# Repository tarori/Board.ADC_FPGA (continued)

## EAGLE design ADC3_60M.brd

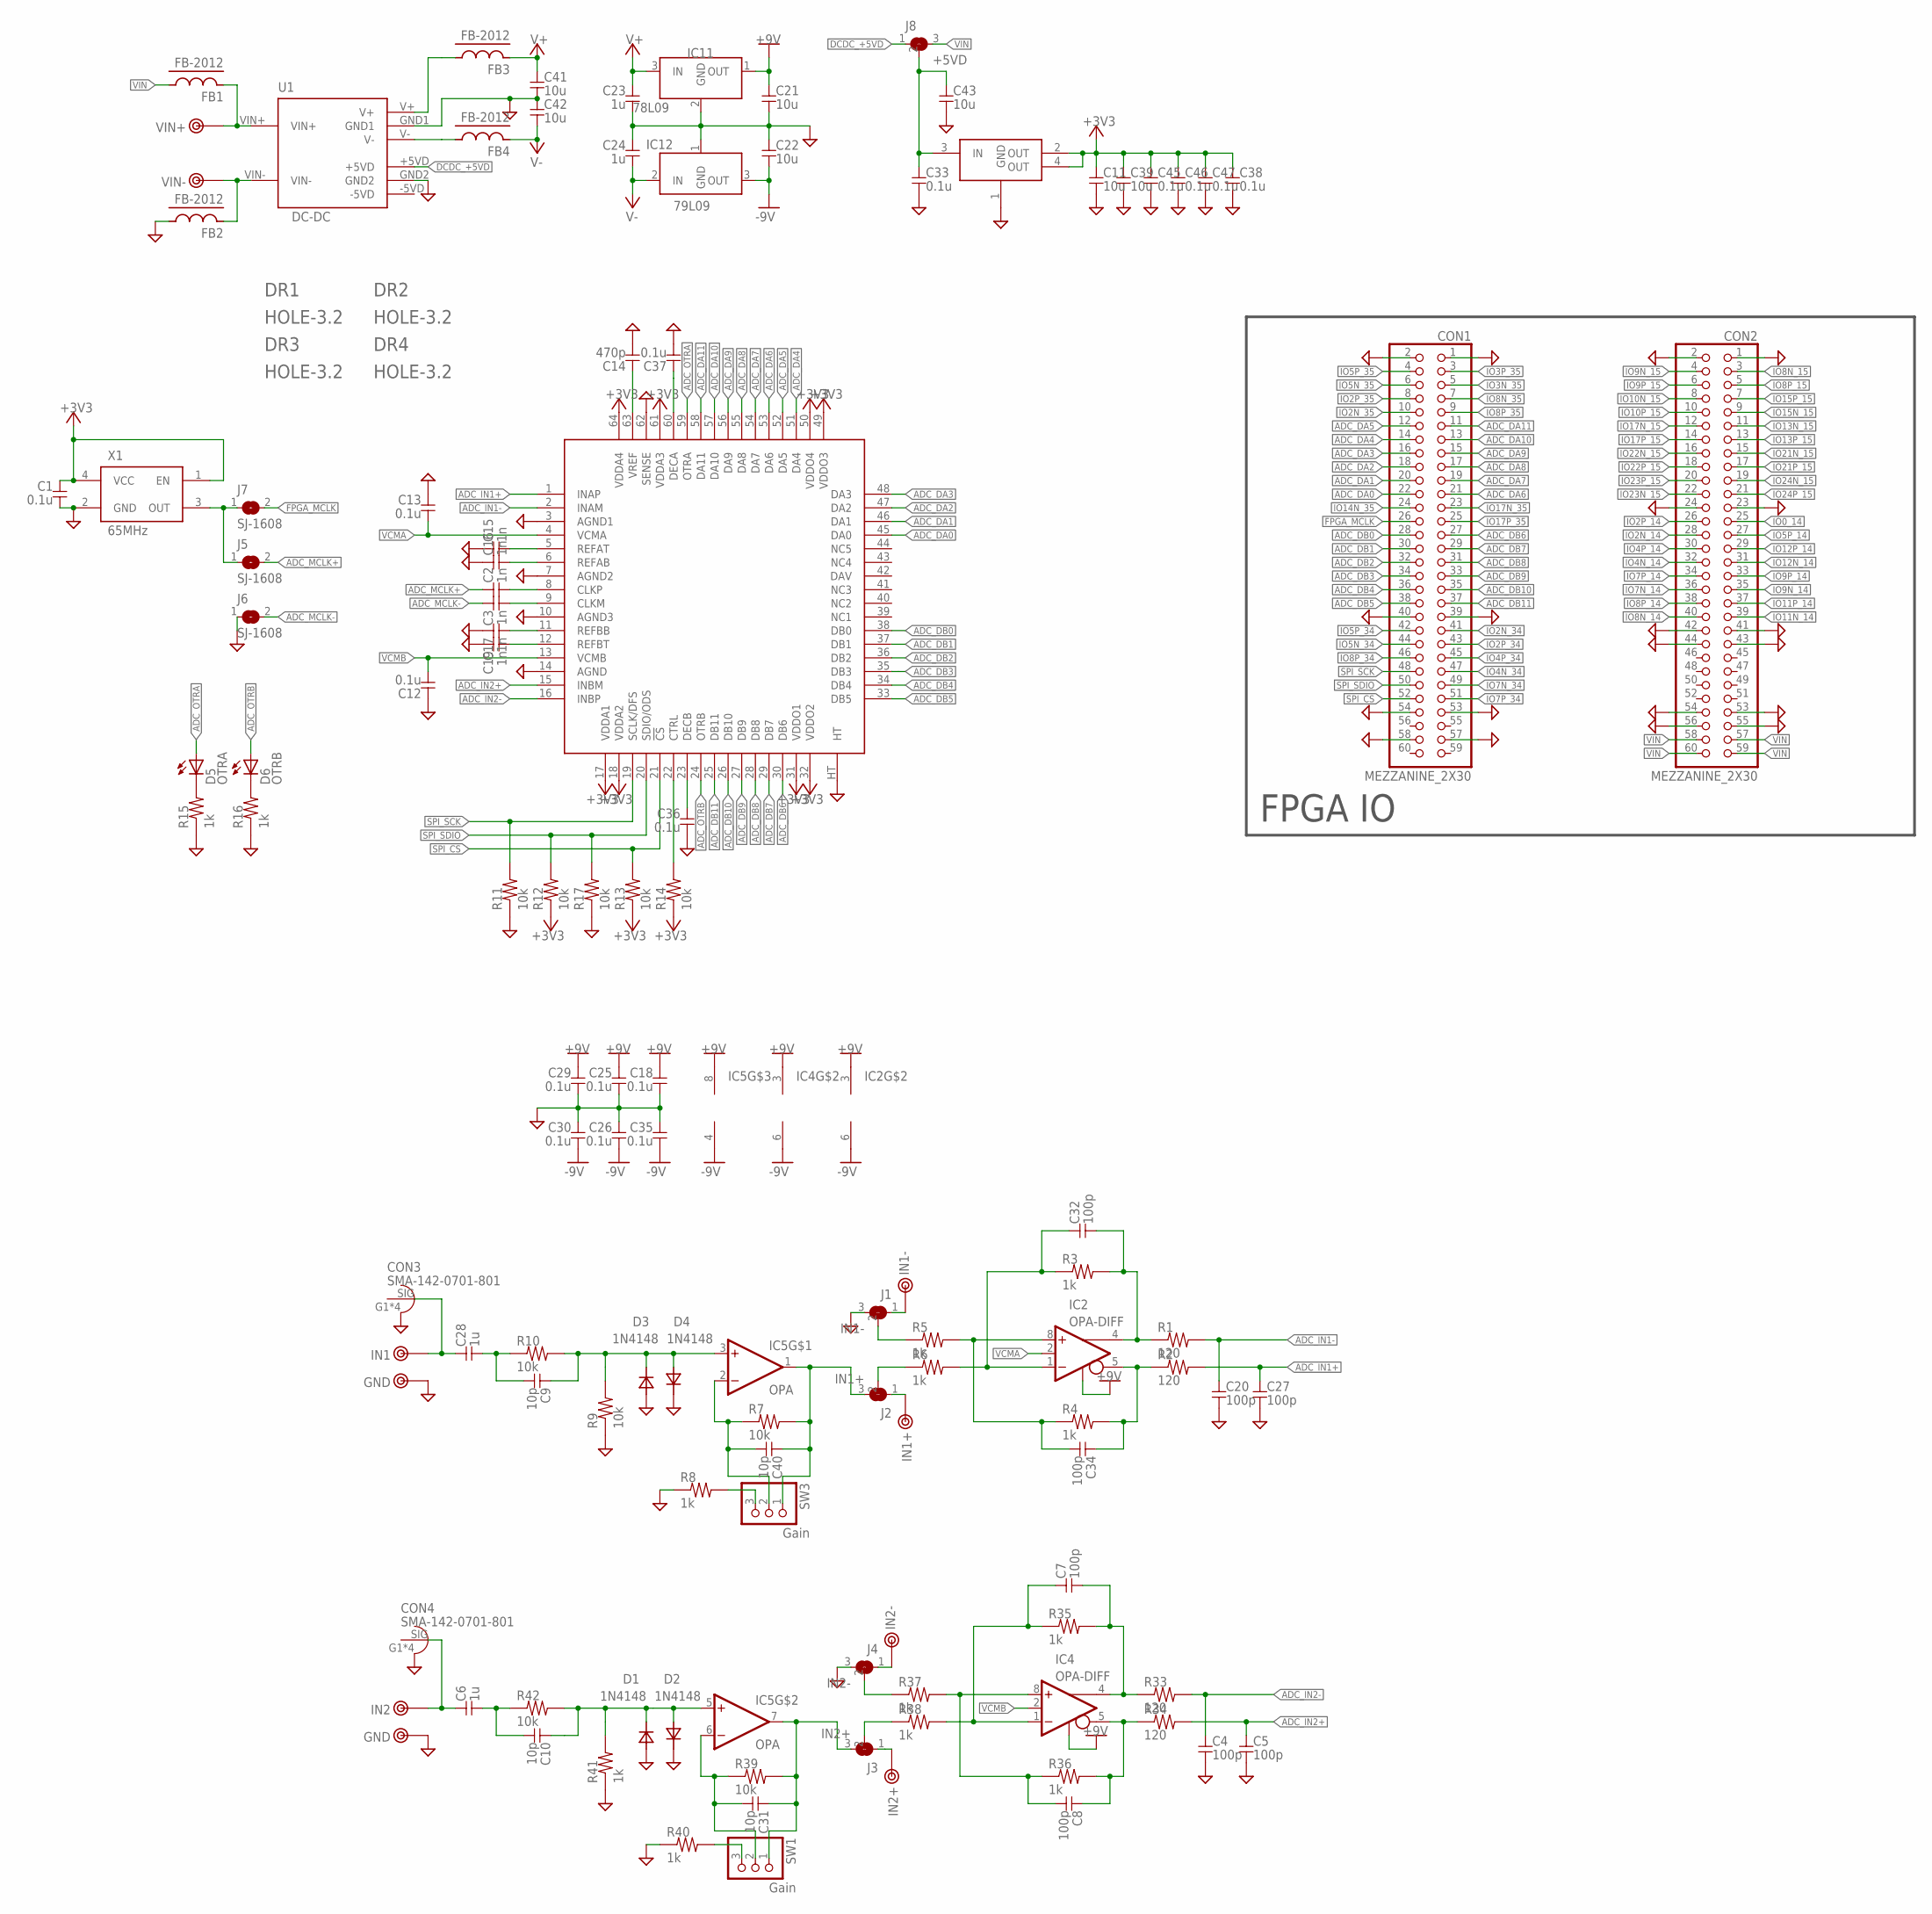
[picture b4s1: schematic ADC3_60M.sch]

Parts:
C1, C12, C13, C18, C25, C26, C29, C30, C33, C35, C36, C37, C38, C45, C46, C47: 0.1u; 1608
C2, C3, C15, C16, C17, C19: 1n; 1608
C4, C5, C7, C8, C20, C27, C32, C34: 100p; 1608
C6, C28: 1u; C050
C9, C10, C31, C40: 10p; 1608
C11, C21, C22, C39, C43: 10u; 2012
C14: 470p; 1608
C23, C24: 1u; 1608
C41, C42: 10u; 3216
CON1, CON2: MEZZANINE_2X30; MEZZANINE_0.8MM_2X30
CON3, CON4: SMA-142-0701-801; SMA-EDGE
D1, D2, D3, D4: 1N4148; SOD123
D5: OTRA; D1608
D6: OTRB; D1608
DR1, DR2, DR3, DR4: HOLE-3.2; HOLE_3.2
FB1, FB2, FB3, FB4: FB-2012; 2012-J
IC1: ADC1212; QFN64HT
IC2, IC4: OPA-DIFF; SOP8
IC5: OPA; SOP8
IC7: AZ1086H-3.3; SOT223
IC11: 78L09; TO-92
IC12: 79L09; TO-92
J1: IN1-; 1608-3-J
J2: IN1+; 1608-3-J
J3: IN2+; 1608-3-J
J4: IN2-; 1608-3-J
J5, J6, J7: SJ-1608; 1608-J
J8: +5VD; 2012-3-J
R1, R2, R33, R34: 120; 1608
R3, R4, R5, R6, R8, R15, R16, R35, R36, R37, R38, R40, R41: 1k; 1608
R7, R9, R10, R11, R12, R13, R14, R17, R39, R42: 10k; 1608
SW1, SW3: Gain; 1X03
TP1: IN2; TESTPIN
TP2, TP5: GND; TESTPIN
TP3: IN2-; TESTPIN
TP4: IN1; TESTPIN
TP6: IN2+; TESTPIN
TP7: IN1-; TESTPIN
TP8: IN1+; TESTPIN
TP30: VIN+; TESTPIN
TP31: VIN-; TESTPIN
U1: DC-DC; DCDC
X1: 65MHz; KC3225

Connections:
+3V3: C1.1, C11.1, C38.1, C39.1, C45.1, C46.1, C47.1, IC1.17 (VDDA1), IC1.18 (VDDA2), IC1.31 (VDDO1), IC1.32 (VDDO2), IC1.49 (VDDO3), IC1.50 (VDDO4), IC1.61 (VDDA3), IC1.64 (VDDA4), IC7.2 (OUT), IC7.4 (OUT), R12.1, R13.1, R14.1, X1.1 (EN), X1.4 (VCC)
+9V: C18.1, C21.1, C25.1, C29.1, IC2.3 (V+), IC2.7 (EN), IC4.3 (V+), IC4.7 (EN), IC5.8 (V+), IC11.1 (OUT)
-9V: C22.2, C26.2, C30.2, C35.2, IC2.6 (V-), IC4.6 (V-), IC5.4 (V-), IC12.3 (OUT)
ADC_DA0: CON1.22, IC1.45 (DA0)
ADC_DA1: CON1.20, IC1.46 (DA1)
ADC_DA2: CON1.18, IC1.47 (DA2)
ADC_DA3: CON1.16, IC1.48 (DA3)
ADC_DA4: CON1.14, IC1.51 (DA4)
ADC_DA5: CON1.12, IC1.52 (DA5)
ADC_DA6: CON1.21, IC1.53 (DA6)
ADC_DA7: CON1.19, IC1.54 (DA7)
ADC_DA8: CON1.17, IC1.55 (DA8)
ADC_DA9: CON1.15, IC1.56 (DA9)
ADC_DA10: CON1.13, IC1.57 (DA10)
ADC_DA11: CON1.11, IC1.58 (DA11)
ADC_DB0: CON1.28, IC1.38 (DB0)
ADC_DB1: CON1.30, IC1.37 (DB1)
ADC_DB2: CON1.32, IC1.36 (DB2)
ADC_DB3: CON1.34, IC1.35 (DB3)
ADC_DB4: CON1.36, IC1.34 (DB4)
ADC_DB5: CON1.38, IC1.33 (DB5)
ADC_DB6: CON1.27, IC1.30 (DB6)
ADC_DB7: CON1.29, IC1.29 (DB7)
ADC_DB8: CON1.31, IC1.28 (DB8)
ADC_DB9: CON1.33, IC1.27 (DB9)
ADC_DB10: CON1.35, IC1.26 (DB10)
ADC_DB11: CON1.37, IC1.25 (DB11)
ADC_IN1+: C27.1, IC1.1 (INAP), R2.2
ADC_IN1-: C20.1, IC1.2 (INAM), R1.2
ADC_IN2+: C5.1, IC1.15 (INBM), R34.2
ADC_IN2-: C4.1, IC1.16 (INBP), R33.2
ADC_MCLK+: C2.1, J5.2
ADC_MCLK-: C3.1, J6.2
ADC_OTRA: D5.A, IC1.59 (OTRA)
ADC_OTRB: D6.A, IC1.24 (OTRB)
DCDC_+5VD: J8.1, U1.+5VD
FPGA_MCLK: CON1.26, J7.2
GND: C1.2, C4.2, C5.2, C11.2, C12.1, C13.1, C14.2, C15.1, C16.1, C17.1, C18.2, C19.1, C20.2, C21.2, C22.1, C23.2, C24.1, C25.2, C26.1, C27.2, C29.2, C30.1, C33.2, C35.1, C36.2, C37.2, C38.2, C39.2, C41.2, C42.1, C43.2, C45.2, C46.2, C47.2, CON1.1, CON1.2, CON1.39, CON1.40, CON1.53, CON1.54, CON1.57, CON1.58, CON2.1, CON2.2, CON2.23, CON2.24, CON2.41, CON2.42, CON2.43, CON2.44, CON2.53, CON2.54, CON2.55, CON2.56, CON3.G1 (GND), CON3.G2 (GND), CON3.G3 (GND), CON3.G4 (GND), CON4.G1 (GND), CON4.G2 (GND), CON4.G3 (GND), CON4.G4 (GND), D1.1 (A), D2.2 (K), D3.1 (A), D4.2 (K), FB2.1, IC1.3 (AGND1), IC1.7 (AGND2), IC1.10 (AGND3), IC1.14 (AGND), IC1.62 (SENSE), IC1.HT, IC7.1 (GND), IC11.2 (GND), IC12.1 (GND), J1.3, J4.3, J6.1, R8.1, R9.1, R11.1, R15.1, R16.1, R17.1, R40.1, R41.1, TP2.1, TP5.1, U1.GND1, U1.GND2, X1.2 (GND)
IO0_14: CON2.25
IO2N_14: CON2.28
IO2N_34: CON1.41
IO2N_35: CON1.10
IO2P_14: CON2.26
IO2P_34: CON1.43
IO2P_35: CON1.8
IO3N_35: CON1.5
IO3P_35: CON1.3
IO4N_14: CON2.32
IO4N_34: CON1.47
IO4P_14: CON2.30
IO4P_34: CON1.45
IO5N_34: CON1.44
IO5N_35: CON1.6
IO5P_14: CON2.27
IO5P_34: CON1.42
IO5P_35: CON1.4
IO7N_14: CON2.36
IO7N_34: CON1.49
IO7P_14: CON2.34
IO7P_34: CON1.51
IO8N_14: CON2.40
IO8N_15: CON2.3
IO8N_35: CON1.7
IO8P_14: CON2.38
IO8P_15: CON2.5
IO8P_34: CON1.46
IO8P_35: CON1.9
IO9N_14: CON2.35
IO9N_15: CON2.4
IO9P_14: CON2.33
IO9P_15: CON2.6
IO10N_15: CON2.8
IO10P_15: CON2.10
IO11N_14: CON2.39
IO11P_14: CON2.37
IO12N_14: CON2.31
IO12P_14: CON2.29
IO13N_15: CON2.11
IO13P_15: CON2.13
IO14N_35: CON1.24
IO15N_15: CON2.9
IO15P_15: CON2.7
IO17N_15: CON2.12
IO17N_35: CON1.23
IO17P_15: CON2.14
IO17P_35: CON1.25
IO21N_15: CON2.15
IO21P_15: CON2.17
IO22N_15: CON2.16
IO22P_15: CON2.18
IO23N_15: CON2.22
IO23P_15: CON2.20
IO24N_15: CON2.19
IO24P_15: CON2.21
MCLK: J5.1, J7.1, X1.3 (OUT)
unnamed: C7.2, IC4.4 (+OUT), R33.1, R35.2
unnamed: C8.1, IC4.5 (-OUT), R34.1, R36.2
unnamed: C8.2, IC4.8 (+IN), R36.1, R37.2
unnamed: R40.2, SW1.3
unnamed: C3.2, IC1.9 (CLKM)
unnamed: C2.2, IC1.8 (CLKP)
unnamed: C14.1, IC1.63 (VREF)
unnamed: C17.2, IC1.11 (REFBB)
unnamed: C19.2, IC1.12 (REFBT)
unnamed: C15.2, IC1.5 (REFAT)
unnamed: C16.2, IC1.6 (REFAB)
unnamed: C7.1, IC4.1 (-IN), R35.1, R38.2
unnamed: C32.2, IC2.4 (+OUT), R1.1, R3.2
unnamed: C34.1, IC2.5 (-OUT), R2.1, R4.2
unnamed: J3.1, TP6.1
unnamed: C31.2, IC5.6 (-IN), R39.1, SW1.2
unnamed: C34.2, IC2.8 (+IN), R4.1, R5.2
unnamed: C32.1, IC2.1 (-IN), R3.1, R6.2
unnamed: C40.1, IC5.1 (OUT), J2.3, R7.2, SW3.1
unnamed: C40.2, IC5.2 (-IN), R7.1, SW3.2
unnamed: C6.1, CON4.SIG, TP1.1
unnamed: C9.2, C28.2, R10.1
unnamed: C9.1, D3.2 (K), D4.1 (A), IC5.3 (+IN), R9.2, R10.2
unnamed: R8.2, SW3.3
unnamed: J1.2, R5.1
unnamed: J2.2, R6.1
unnamed: J3.2, R38.1
unnamed: C28.1, CON3.SIG, TP4.1
unnamed: J4.2, R37.1
unnamed: C31.1, IC5.7 (OUT), J3.3, R39.2, SW1.1
unnamed: J4.1, TP3.1
unnamed: J2.1, TP8.1
unnamed: J1.1, TP7.1
unnamed: C33.1, C43.1, IC7.3 (IN), J8.2
unnamed: C6.2, C10.2, R42.1
unnamed: C10.1, D1.2 (K), D2.1 (A), IC5.5 (+IN), R41.2, R42.2
unnamed: C37.1, IC1.60 (DECA)
unnamed: D6.K, R16.2
unnamed: D5.K, R15.2
unnamed: IC1.22 (CTRL), R14.2
unnamed: C36.1, IC1.23 (DECB)
unnamed: FB1.2, TP30.1, U1.VIN+
unnamed: FB2.2, TP31.1, U1.VIN-
SPI_CS: CON1.52, IC1.21 (!CS), R13.2
SPI_SCK: CON1.48, IC1.19 (SCLK/DFS), R11.2
SPI_SDIO: CON1.50, IC1.20 (SDIO/ODS), R12.2, R17.2
V+: C23.1, C41.1, FB3.2, IC11.3 (IN)
V+_DCDC: FB3.1, U1.V+
V-: C24.2, C42.2, FB4.2, IC12.2 (IN)
V-_DCDC: FB4.1, U1.V-
VCMA: C13.2, IC1.4 (VCMA), IC2.2 (CM)
VCMB: C12.2, IC1.13 (VCMB), IC4.2 (CM)
VIN: CON2.57, CON2.58, CON2.59, CON2.60, FB1.1, J8.3

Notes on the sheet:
FPGA IO

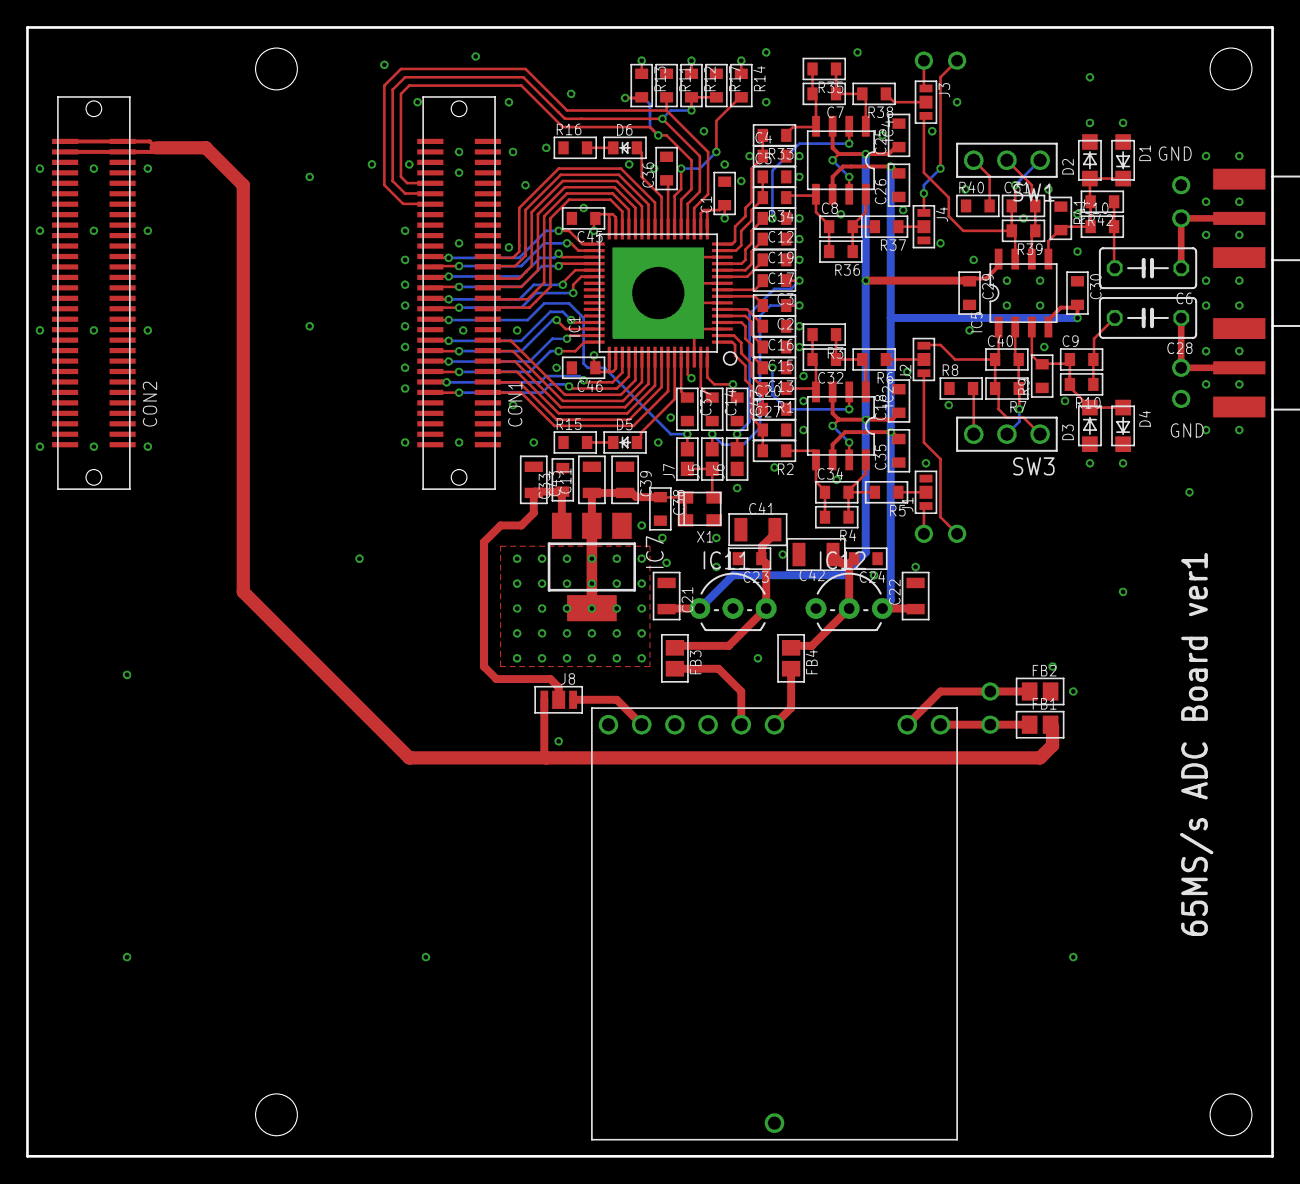
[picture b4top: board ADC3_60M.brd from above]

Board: 4 copper layers, 95.2 x 86.4 mm, 120 parts (0 on the bottom side), 92 nets.

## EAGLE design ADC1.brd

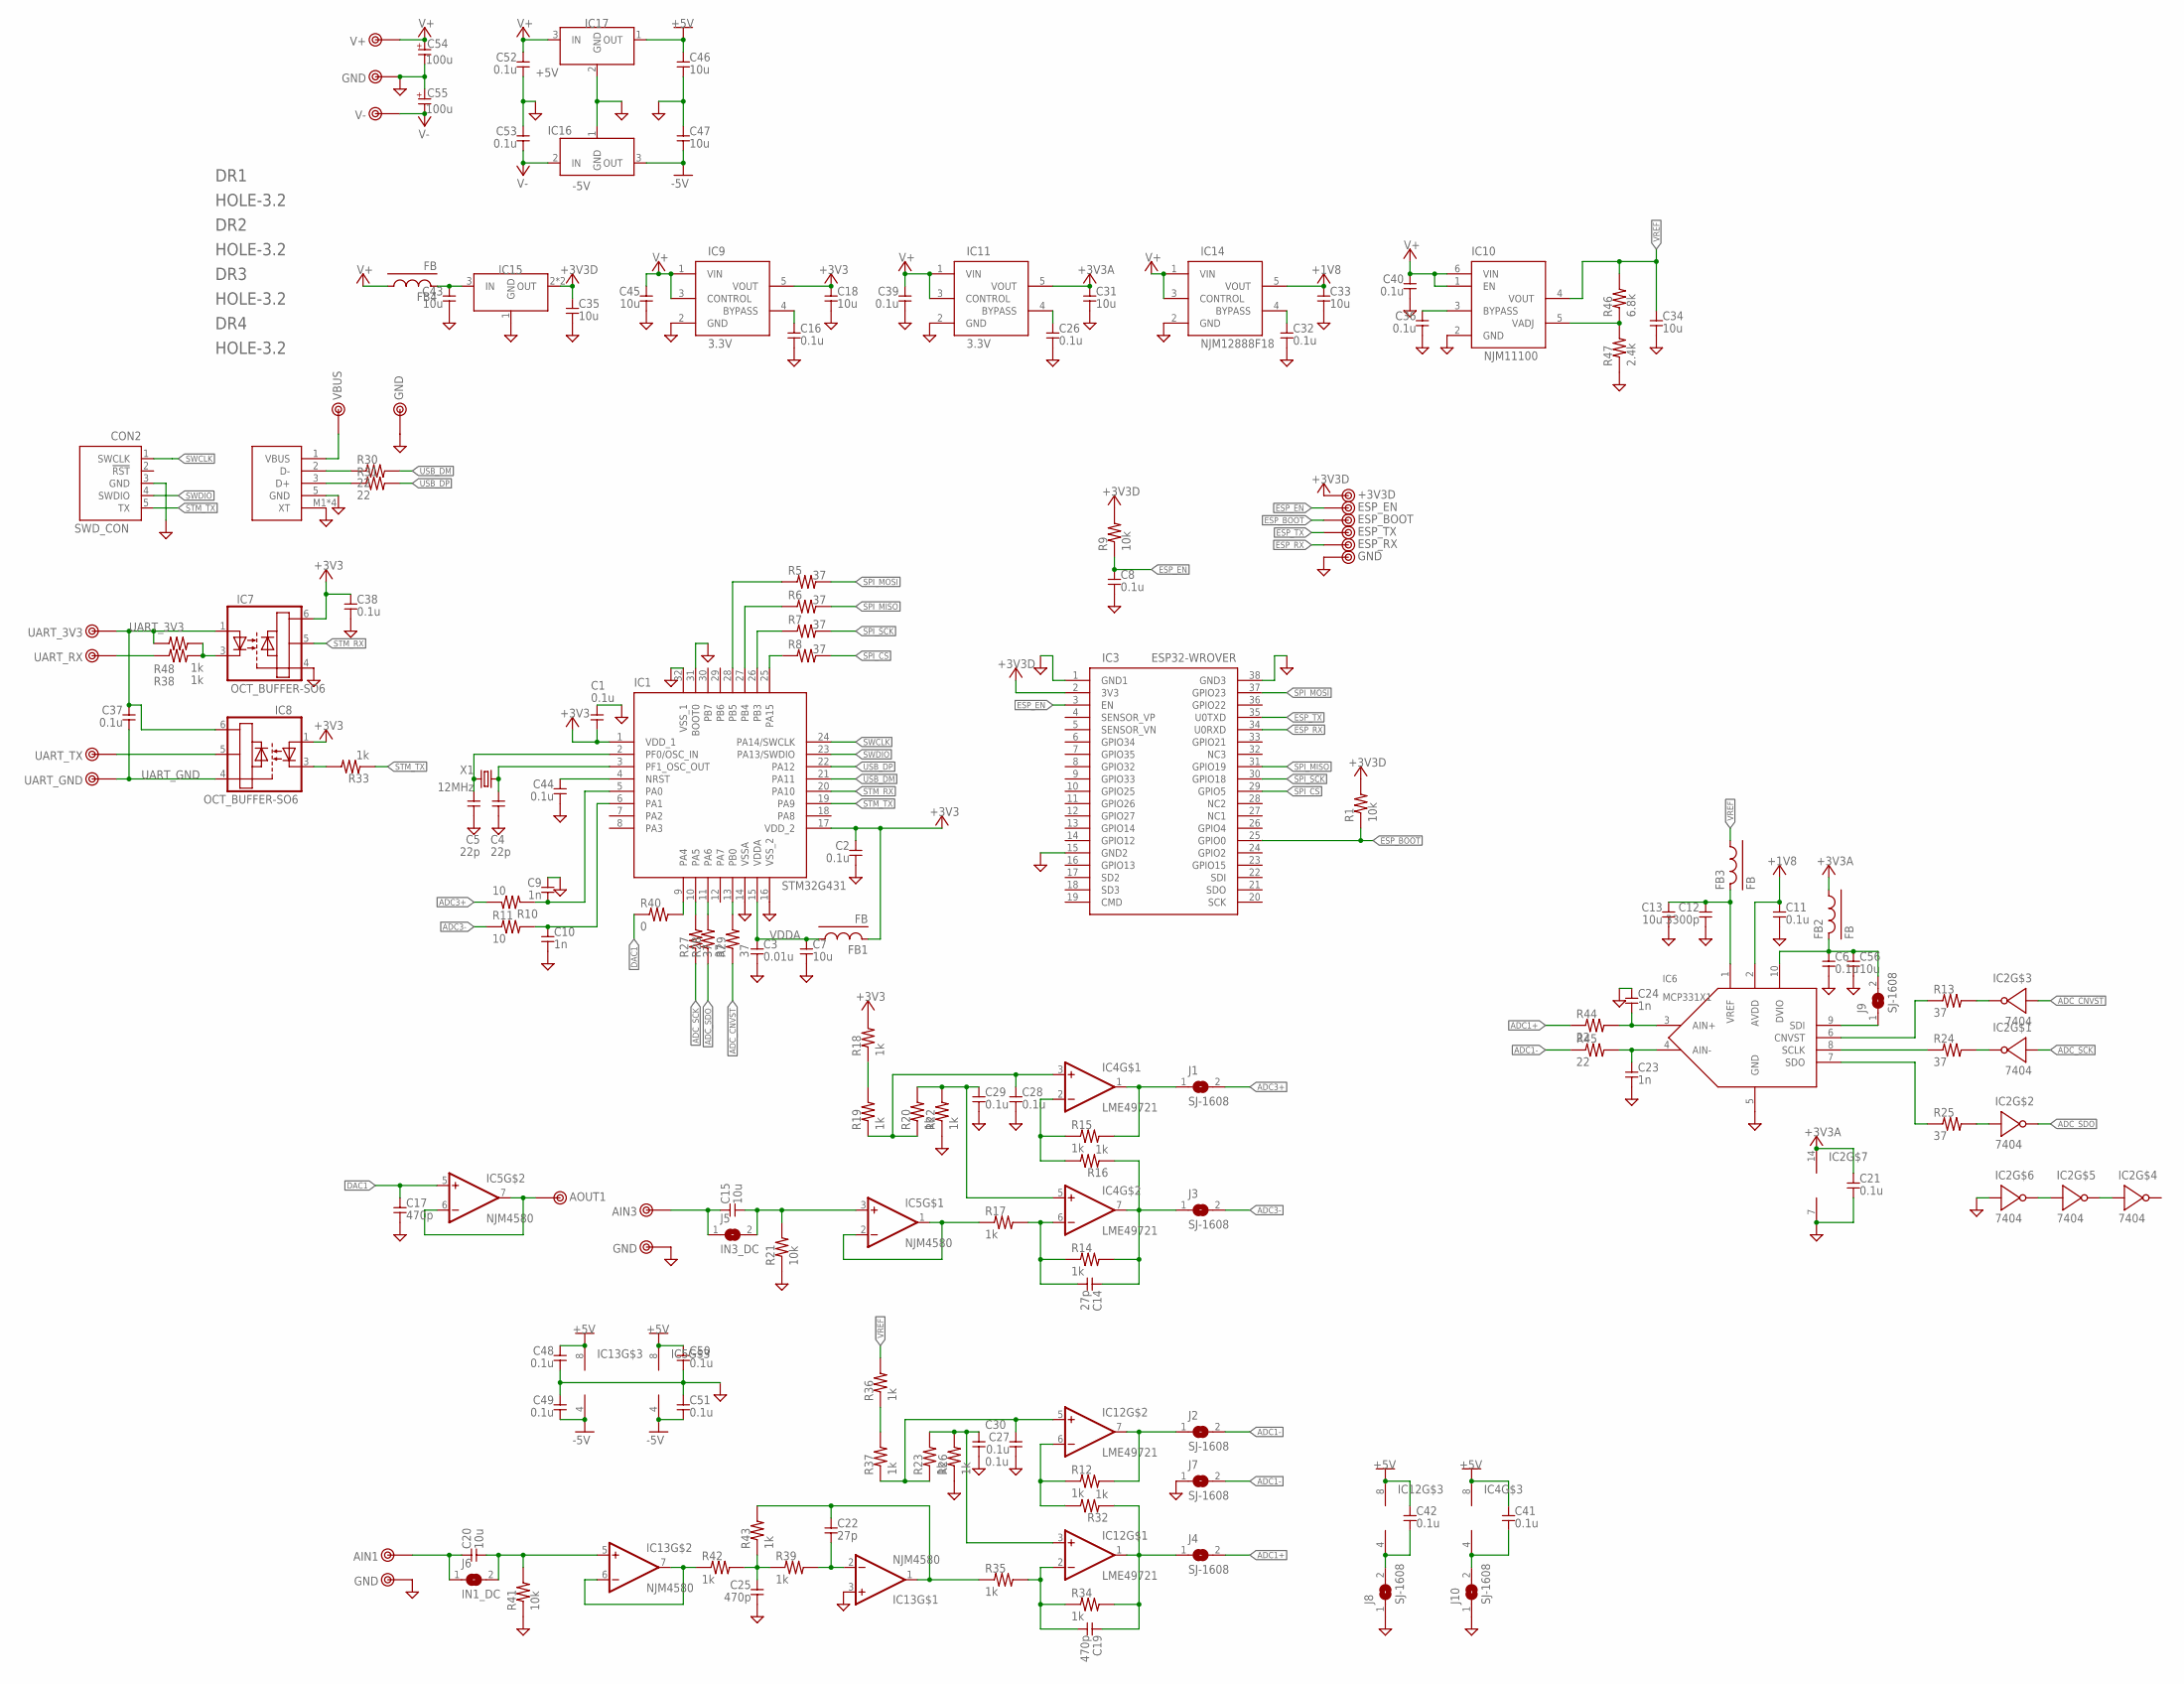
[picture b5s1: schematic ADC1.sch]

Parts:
C1, C2, C6, C8, C11, C16, C21, C26, C27, C28, C29, C30, C32, C36, C37, C38, C39, C40, C41, C42, C44, C48, C49, C50, C51, C52, C53: 0.1u; 1608
C3: 0.01u; 1608
C4, C5: 22p; 1608
C7, C13, C18, C31, C33, C34, C35, C43, C45, C46, C47, C56: 10u; 2012
C9, C10, C23, C24: 1n; 1608
C12: 3300p; 1608
C14, C22: 27p; 1608
C15, C20: 10u; 3225
C17, C19, C25: 470p; 1608
C54, C55: 100u; E2,5-8
CON1: USB-A; UX60A-MB-5ST
CON2: SWD_CON
DR1, DR2, DR3, DR4: HOLE-3.2; HOLE_3.2
FB1, FB2, FB3, FB4: FB; 1608-J
IC1: STM32G431; TQFP32-08
IC2: 7404; TSSOP14
IC3: ESP32-WROVER
IC4, IC12: LME49721; SOP8
IC5, IC13: NJM4580; SOP8
IC6: MCP331X1; MSOP10
IC7, IC8: OCT_BUFFER-SO6; SO6
IC9, IC11: 3.3V; SOT23-5
IC10: NJM11100; SOT23-6
IC14: NJM12888F18; SOT23-5
IC15: LM1117GS; SOT223
IC16: -5V; TO-92
IC17: +5V; TO-92
J1, J2, J3, J4, J7, J8, J9, J10: SJ-1608; 1608-J
J5: IN3_DC; 2012-J
J6: IN1_DC; 2012-J
R1, R9, R21, R41: 10k; 1608
R5, R6, R7, R8, R13, R24, R25, R27, R28, R29: 37; 1608-J
R10, R11: 10; 1608
R12, R14, R15, R16, R17, R18, R19, R20, R22, R23, R26, R32, R33, R34, R35, R36, R37, R38, R39, R42, R43, R48: 1k; 1608
R30, R31, R44, R45: 22; 1608
R40: 0; 1608-J
R46: 6.8k; 1608
R47: 2.4k; 1608
TP1: AIN3; TESTPIN-BIG
TP2: AIN1; TESTPIN-BIG
TP3: AOUT1; TESTPIN-BIG
TP4: VBUS; TESTPIN
TP5: UART_3V3; TESTPIN
TP6: UART_RX; TESTPIN
TP7: UART_GND; TESTPIN
TP8: UART_TX; TESTPIN
TP9: +3V3D; TESTPIN
TP10: ESP_EN; TESTPIN
TP11: ESP_BOOT; TESTPIN
TP12: ESP_TX; TESTPIN
TP13, TP20: GND; TESTPIN
TP14: ESP_RX; TESTPIN
TP15, TP16, TP18: GND; TESTPIN-BIG
TP17: V+; TESTPIN-BIG
TP19: V-; TESTPIN-BIG
X1: 12MHz; HC49/S

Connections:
+1V8: C11.1, C33.1, IC6.2 (AVDD), IC14.5 (VOUT)
+3V3: C1.2, C2.1, C18.1, C38.1, FB1.2, IC1.1 (VDD_1), IC1.17 (VDD_2), IC7.6 (V+), IC8.1 (A), IC9.5 (VOUT), R18.2
+3V3A: C21.1, C31.1, FB2.1, IC2.14 (V+), IC11.5 (VOUT)
+3V3D: C35.1, IC3.2 (3V3), IC15.2 (OUT), IC15.4 (OUT), R1.2, R9.2, TP9.1
+5V: C41.1, C42.1, C46.1, C48.1, C50.1, IC4.8 (V+), IC5.8 (V+), IC12.8 (V+), IC13.8 (V+), IC17.1 (OUT)
-5V: C47.2, C49.2, C51.2, IC5.4 (V-), IC13.4 (V-), IC16.3 (OUT)
ADC1+: J4.2, R44.1
ADC1-: J2.2, J7.2, R45.1
ADC3+: J1.2, R10.1
ADC3-: J3.2, R11.1
ADC_CNVST: IC2.5 (IN), R29.1
ADC_SCK: IC2.1 (IN), R27.1
ADC_SDO: IC2.4 (OUT), R28.1
DAC1: C17.1, IC5.5 (+IN), R40.1
ESP_BOOT: IC3.25 (GPIO0), R1.1, TP11.1
ESP_EN: C8.1, IC3.3 (EN), R9.1, TP10.1
ESP_RX: IC3.34 (U0RXD), TP14.1
ESP_TX: IC3.35 (U0TXD), TP12.1
GND: C1.1, C2.2, C3.2, C4.2, C5.2, C6.2, C7.2, C8.2, C9.1, C10.2, C11.2, C12.2, C13.2, C16.2, C17.2, C18.2, C21.2, C23.2, C24.1, C25.2, C26.2, C27.2, C28.2, C29.2, C30.2, C31.2, C32.2, C33.2, C34.2, C35.2, C36.2, C38.2, C39.2, C40.2, C43.2, C44.2, C45.2, C46.2, C47.1, C48.2, C49.1, C50.2, C51.1, C52.2, C53.1, C54.- (2), C55.+ (1), C56.2, CON1.5 (GND), CON1.M1 (XT), CON1.M2 (XT), CON1.M3 (XT), CON1.M4 (XT), CON2.3 (GND), IC1.14 (VSSA), IC1.16 (VSS_2), IC1.31 (BOOT0), IC1.32 (VSS_1), IC2.7 (V-), IC2.13 (IN), IC3.1 (GND1), IC3.15 (GND2), IC3.38 (GND3), IC6.5 (GND), IC7.4 (GND), IC9.2 (GND), IC10.2 (GND), IC11.2 (GND), IC13.3 (+IN), IC14.2 (GND), IC15.1 (GND), IC16.1 (GND), IC17.2 (GND), J7.1, J8.1, J10.1, R21.1, R22.1, R26.1, R41.1, R47.1, TP13.1, TP15.1, TP16.1, TP18.1, TP20.1
unnamed: C5.1, IC1.2 (PF0/OSC_IN), X1.2
unnamed: C9.2, IC1.5 (PA0), R10.2
unnamed: C4.1, IC1.3 (PF1_OSC_OUT), X1.1
unnamed: C25.1, R39.1, R42.2, R43.1
unnamed: C10.1, IC1.6 (PA1), R11.2
unnamed: IC1.26 (PB3), R7.1
unnamed: IC1.27 (PB4), R6.1
unnamed: IC1.28 (PB5), R5.1
unnamed: IC1.13 (PB0), R29.2
unnamed: C15.1, J5.1, TP1.1
unnamed: IC2.11 (IN), IC2.12 (OUT)
unnamed: IC2.9 (IN), IC2.10 (OUT)
unnamed: C28.1, IC4.3 (+IN), R19.1, R20.1
unnamed: C6.1, C56.1, FB2.2, IC6.10 (DVIO), J9.2
unnamed: C12.1, C13.1, FB3.2, IC6.1 (VREF)
unnamed: IC1.25 (PA15), R8.1
unnamed: IC4.2 (-IN), R15.1, R16.2
unnamed: IC2.6 (OUT), R13.2
unnamed: IC2.3 (IN), R25.2
unnamed: C14.2, IC4.6 (-IN), R14.1, R17.2
unnamed: C15.2, IC5.3 (+IN), J5.2, R21.2
unnamed: IC5.1 (OUT), IC5.2 (-IN), R17.1
unnamed: IC5.6 (-IN), IC5.7 (OUT), TP3.1
unnamed: IC6.7 (SDO), R25.1
unnamed: IC4.1 (OUT), J1.1, R15.2
unnamed: C14.1, IC4.7 (OUT), J3.1, R14.2, R16.1
unnamed: IC6.8 (SCLK), R24.1
unnamed: IC6.6 (CNVST), R13.1
unnamed: IC6.9 (SDI), J9.1
unnamed: IC2.2 (OUT), R24.2
unnamed: CON1.2 (D-), R30.1
unnamed: CON1.3 (D+), R31.1
unnamed: IC8.3 (C), R33.2
unnamed: IC7.3 (C), R38.2, R48.2
unnamed: IC1.10 (PA5), R27.2
unnamed: IC1.11 (PA6), R28.2
unnamed: R36.1, R37.2
unnamed: C29.1, IC4.5 (+IN), R20.2, R22.2
unnamed: R18.1, R19.2
unnamed: C27.1, IC12.5 (+IN), R23.1, R37.1
unnamed: IC12.6 (-IN), R12.1, R32.2
unnamed: C19.2, IC12.2 (-IN), R34.1, R35.2
unnamed: C30.1, IC12.3 (+IN), R23.2, R26.2
unnamed: IC13.6 (-IN), IC13.7 (OUT), R42.1
unnamed: IC12.7 (OUT), J2.1, R12.2
unnamed: C19.1, IC12.1 (OUT), J4.1, R32.1, R34.2
unnamed: C20.1, J6.1, TP2.1
unnamed: C20.2, IC13.5 (+IN), J6.2, R41.2
unnamed: C16.1, IC9.4 (BYPASS)
unnamed: C24.2, IC6.3 (AIN+), R44.2
unnamed: C23.1, IC6.4 (AIN-), R45.2
unnamed: IC1.9 (PA4), R40.2
unnamed: C22.2, IC13.2 (-IN), R39.2
unnamed: C26.1, IC11.4 (BYPASS)
unnamed: C22.1, IC13.1 (OUT), R35.1, R43.2
unnamed: C32.1, IC14.4 (BYPASS)
unnamed: C36.1, IC10.3 (BYPASS)
unnamed: IC10.5 (VADJ), R46.1, R47.2
unnamed: C42.2, IC12.4 (V-), J8.2
unnamed: C41.2, IC4.4 (V-), J10.2
unnamed: C43.1, FB4.2, IC15.3 (IN)
unnamed: C44.1, IC1.4 (NRST)
SPI_CS: IC3.29 (GPIO5), R8.2
SPI_MISO: IC3.31 (GPIO19), R6.2
SPI_MOSI: IC3.37 (GPIO23), R5.2
SPI_SCK: IC3.30 (GPIO18), R7.2
STM_RX: IC1.20 (PA10), IC7.5 (OUT)
STM_TX: CON2.5 (TX), IC1.19 (PA9), R33.1
SWCLK: CON2.1 (SWCLK), IC1.24 (PA14/SWCLK)
SWDIO: CON2.4 (SWDIO), IC1.23 (PA13/SWDIO)
UART_3V3: C37.1, IC7.1 (A), IC8.6 (V+), R48.1, TP5.1
UART_GND: C37.2, IC8.4 (GND), TP7.1
UART_RX: R38.1, TP6.1
UART_TX: IC8.5 (OUT), TP8.1
USB_DM: IC1.21 (PA11), R30.2
USB_DP: IC1.22 (PA12), R31.2
V+: C39.1, C40.1, C45.1, C52.1, C54.+ (1), FB4.1, IC9.1 (VIN), IC9.3 (CONTROL), IC10.1 (EN), IC10.6 (VIN), IC11.1 (VIN), IC11.3 (CONTROL), IC14.1 (VIN), IC14.3 (CONTROL), IC17.3 (IN), TP17.1
V-: C53.2, C55.- (2), IC16.2 (IN), TP19.1
VBUS: CON1.1 (VBUS), TP4.1
VDDA: C3.1, C7.1, FB1.1, IC1.15 (VDDA)
VREF: C34.1, FB3.1, IC10.4 (VOUT), R36.2, R46.2

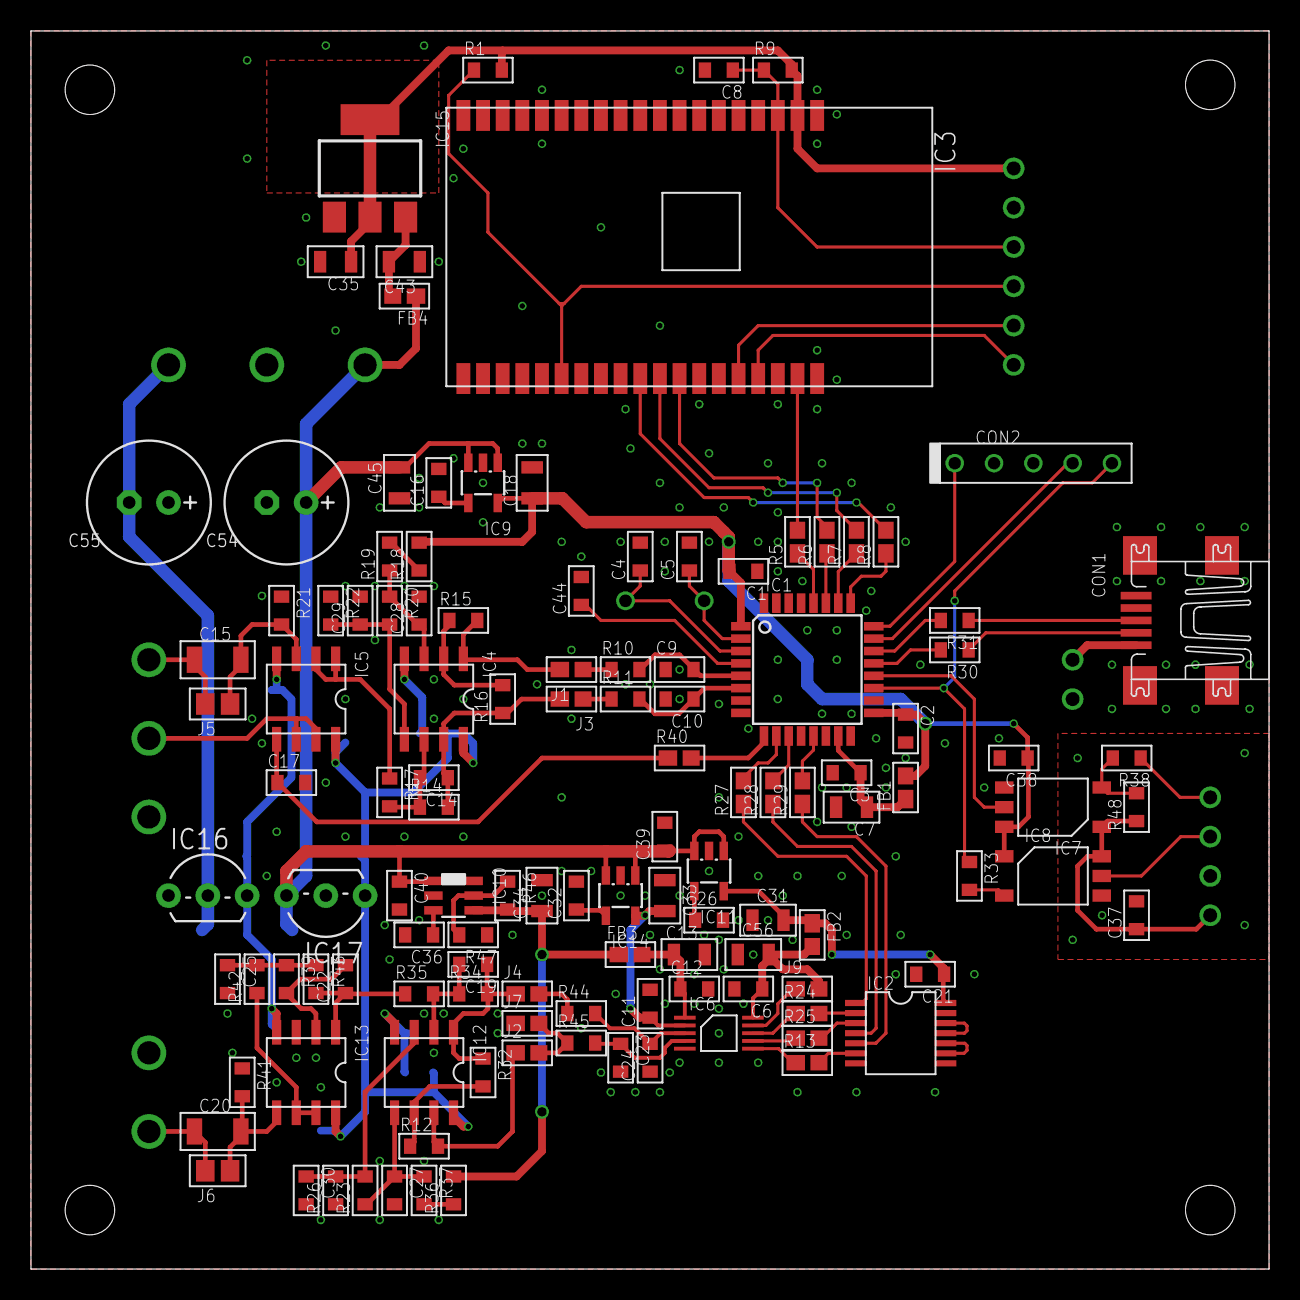
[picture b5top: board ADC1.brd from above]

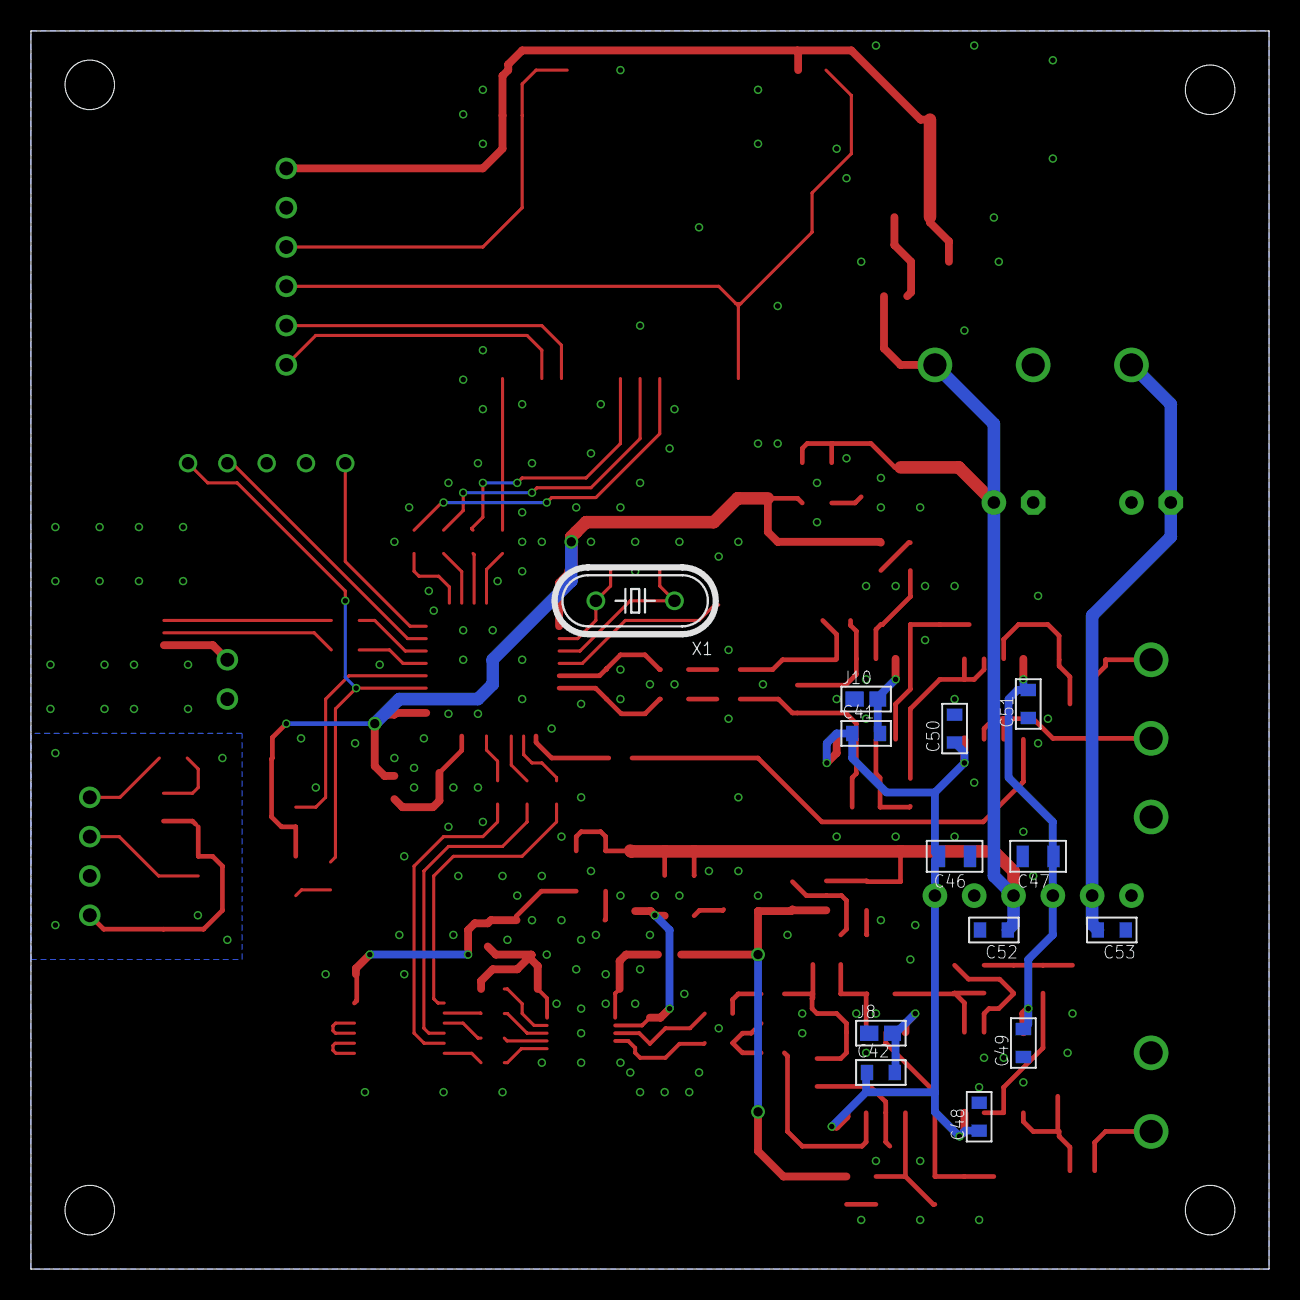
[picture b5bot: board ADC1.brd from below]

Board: 4 copper layers, 80.0 x 80.0 mm, 159 parts (13 on the bottom side), 100 nets.

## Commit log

2022-09-03 initial
2022-09-11 ほぼ完成
2022-11-08 ver2
2023-08-13 ver2修正
2023-08-18 60MS/sを発注
2025-02-01 1kHz BPF
2025-02-04 AD4134
2025-12-31 入力回路変更
